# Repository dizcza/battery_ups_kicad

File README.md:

# Battery UPS Kicad design

* BMS-2S-2P (2 cells with 2 parallel batteries each) HX-2S-JH20
* Support both 18650 and 21700 Li-Ion batteries
* XL4015 StepDown: 12V -> 8.4V
* A very cheap StepUp: 8.4V -> 12V
* Fuse 5A, switch, battery capacity tester
* Diodes to bypass current if mains is powered
* DC 5.5 2.1 input and output jackets

[Schematics](./schematics.pdf)

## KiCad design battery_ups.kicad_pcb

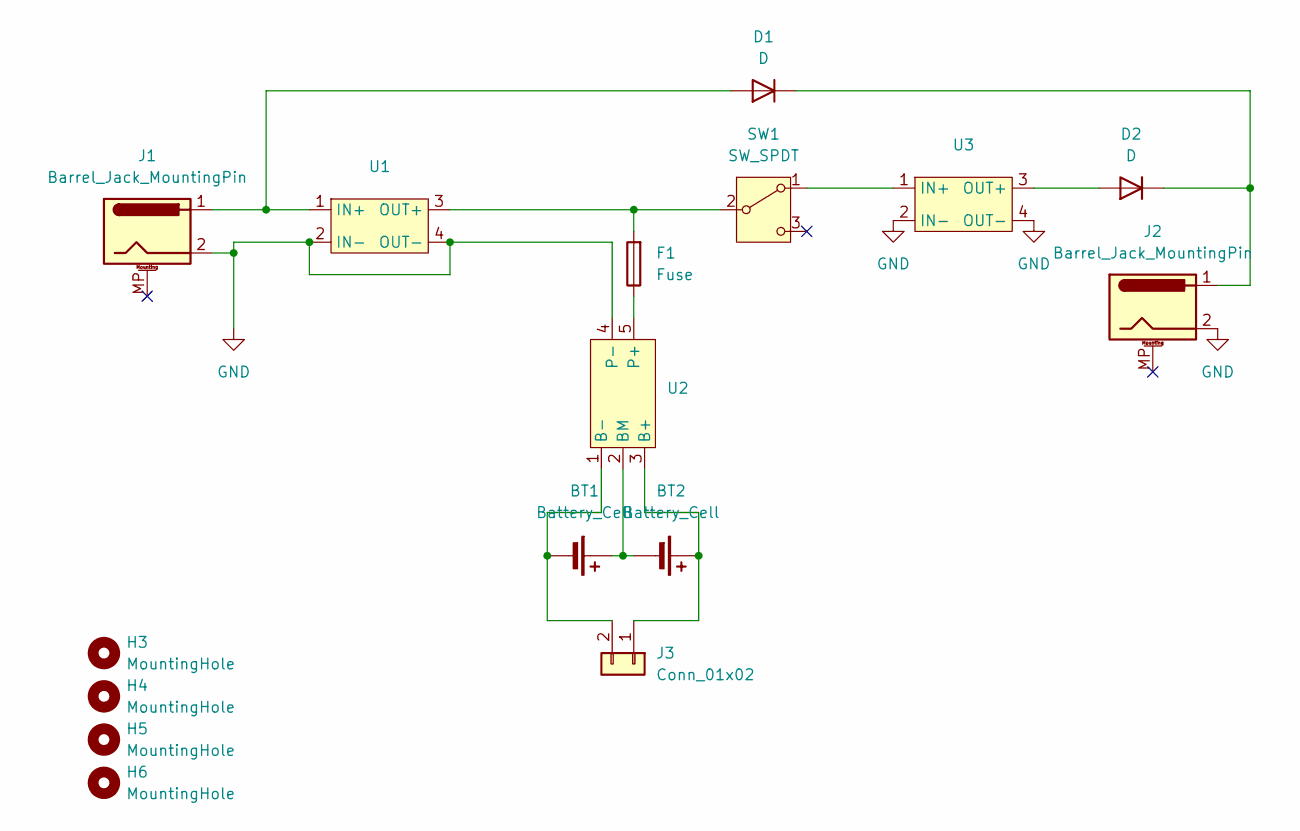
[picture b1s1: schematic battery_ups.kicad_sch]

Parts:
BT1, BT2: Battery_Cell; BAT_BK-18650-21700
D1, D2: D; D_P600_R-6_P12.70mm_Horizontal
F1: Fuse; Fuse-5x20
H3, H4, H5, H6: MountingHole; MountingHole_4.3mm_M4
J1, J2: Barrel_Jack_MountingPin; BarrelJack_Horizontal
J3: Conn_01x02; BattTester
SW1: SW_SPDT; SW-TH_SS-12D11G5R
U1: XL4015_StepDown
U2: HX-2S-JH20
U3: StepUp12V

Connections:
GND: J1.2, J2.2, U1.2 (IN-), U1.4 (OUT-), U2.4 (P-), U3.2 (IN-), U3.4 (OUT-)
unnamed: BT1.1 (+), BT2.2 (-), U2.2 (BM)
unnamed: BT1.2 (-), J3.2, U2.1 (B-)
unnamed: BT2.1 (+), J3.1, U2.3 (B+)
unnamed: D1.2 (A), J1.1, U1.1 (IN+)
unnamed: D1.1 (K), D2.1 (K), J2.1
unnamed: D2.2 (A), U3.3 (OUT+)
unnamed: SW1.1 (A), U3.1 (IN+)
unnamed: F1.2, SW1.2 (B), U1.3 (OUT+)
unnamed: F1.1, U2.5 (P+)

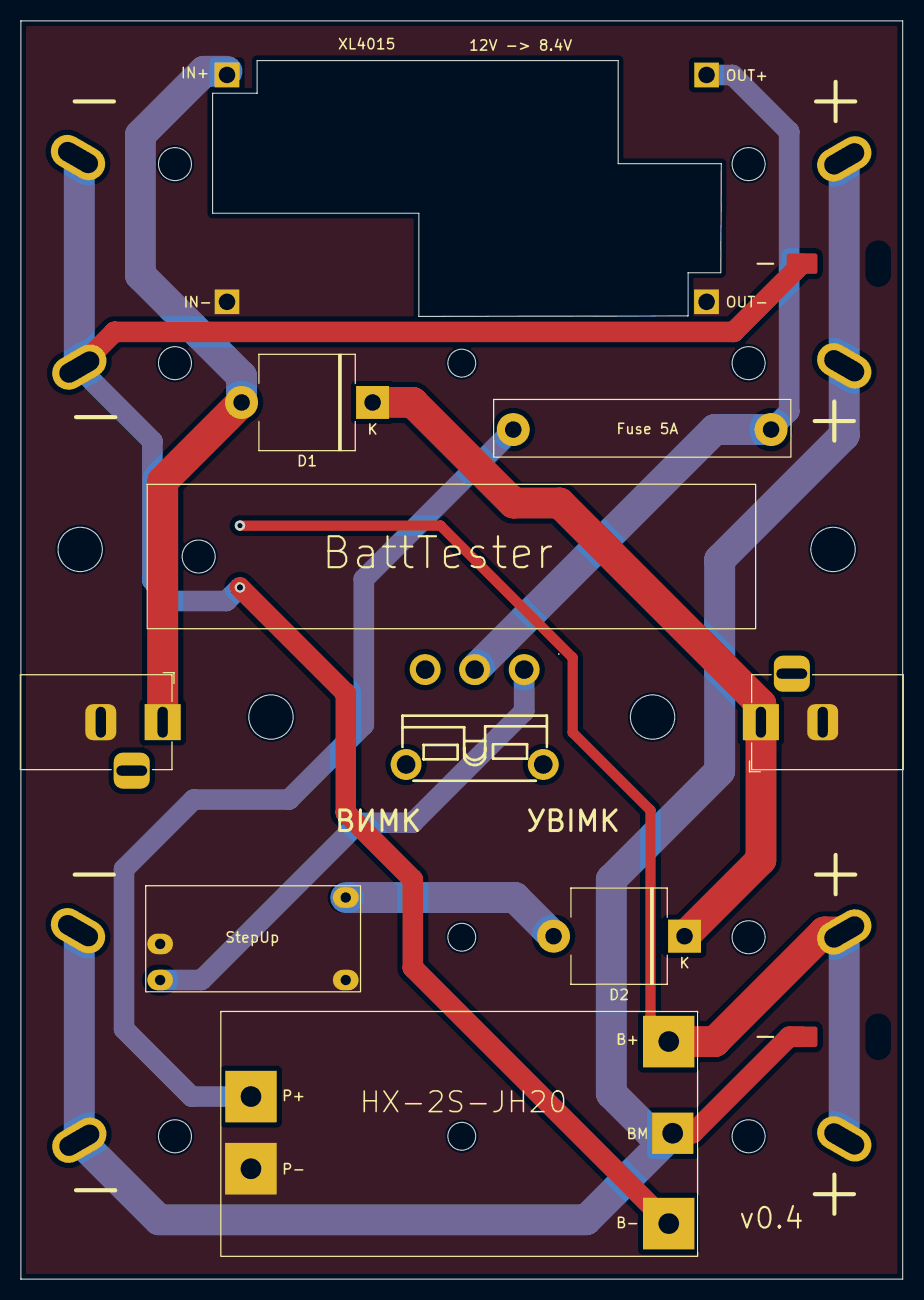
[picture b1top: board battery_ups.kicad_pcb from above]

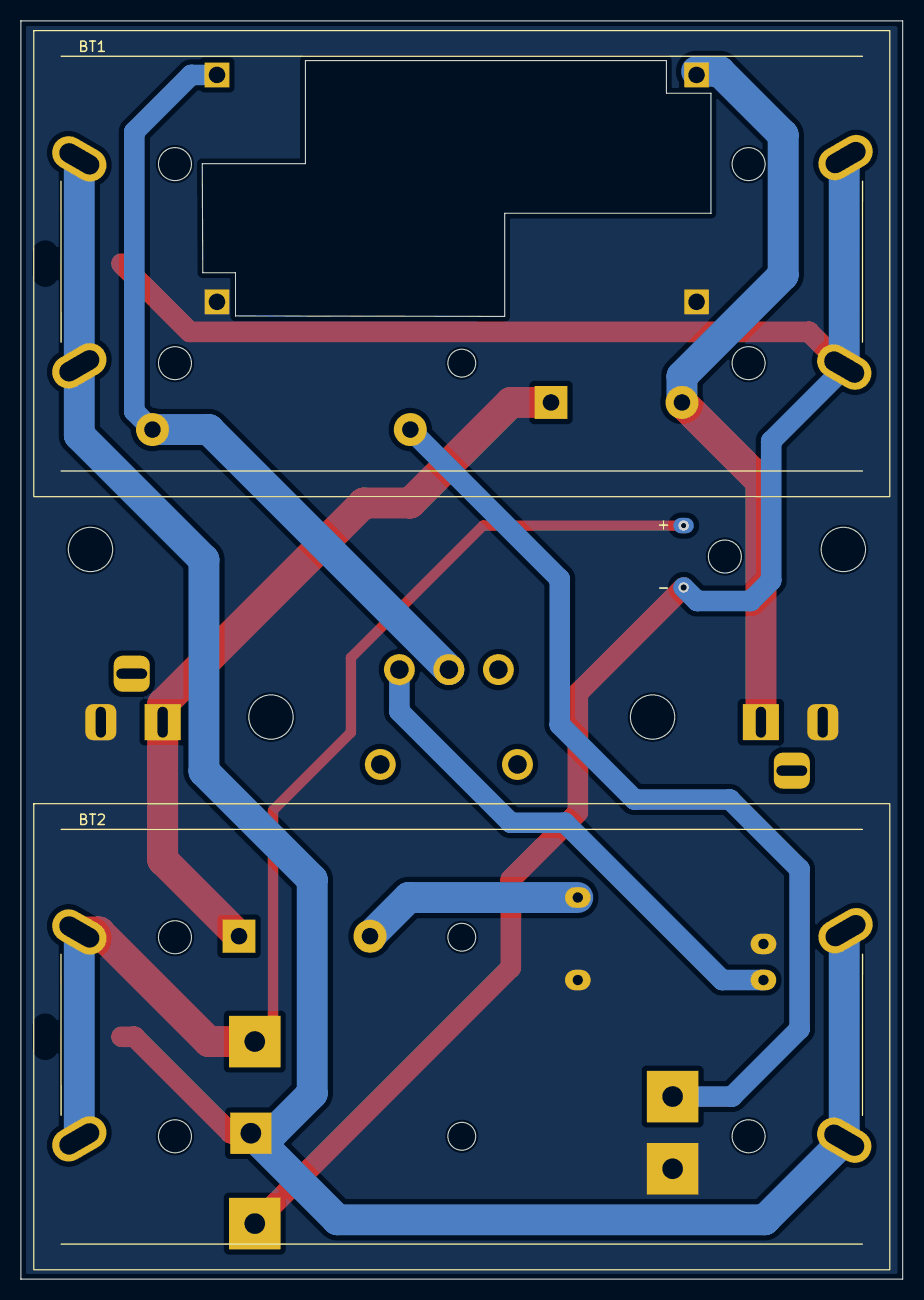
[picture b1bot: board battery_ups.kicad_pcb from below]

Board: 2 copper layers, 85.5 x 122.0 mm, 16 parts (2 on the bottom side), 10 nets.

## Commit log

2024-11-20 v0.4: bms-2s-2p
